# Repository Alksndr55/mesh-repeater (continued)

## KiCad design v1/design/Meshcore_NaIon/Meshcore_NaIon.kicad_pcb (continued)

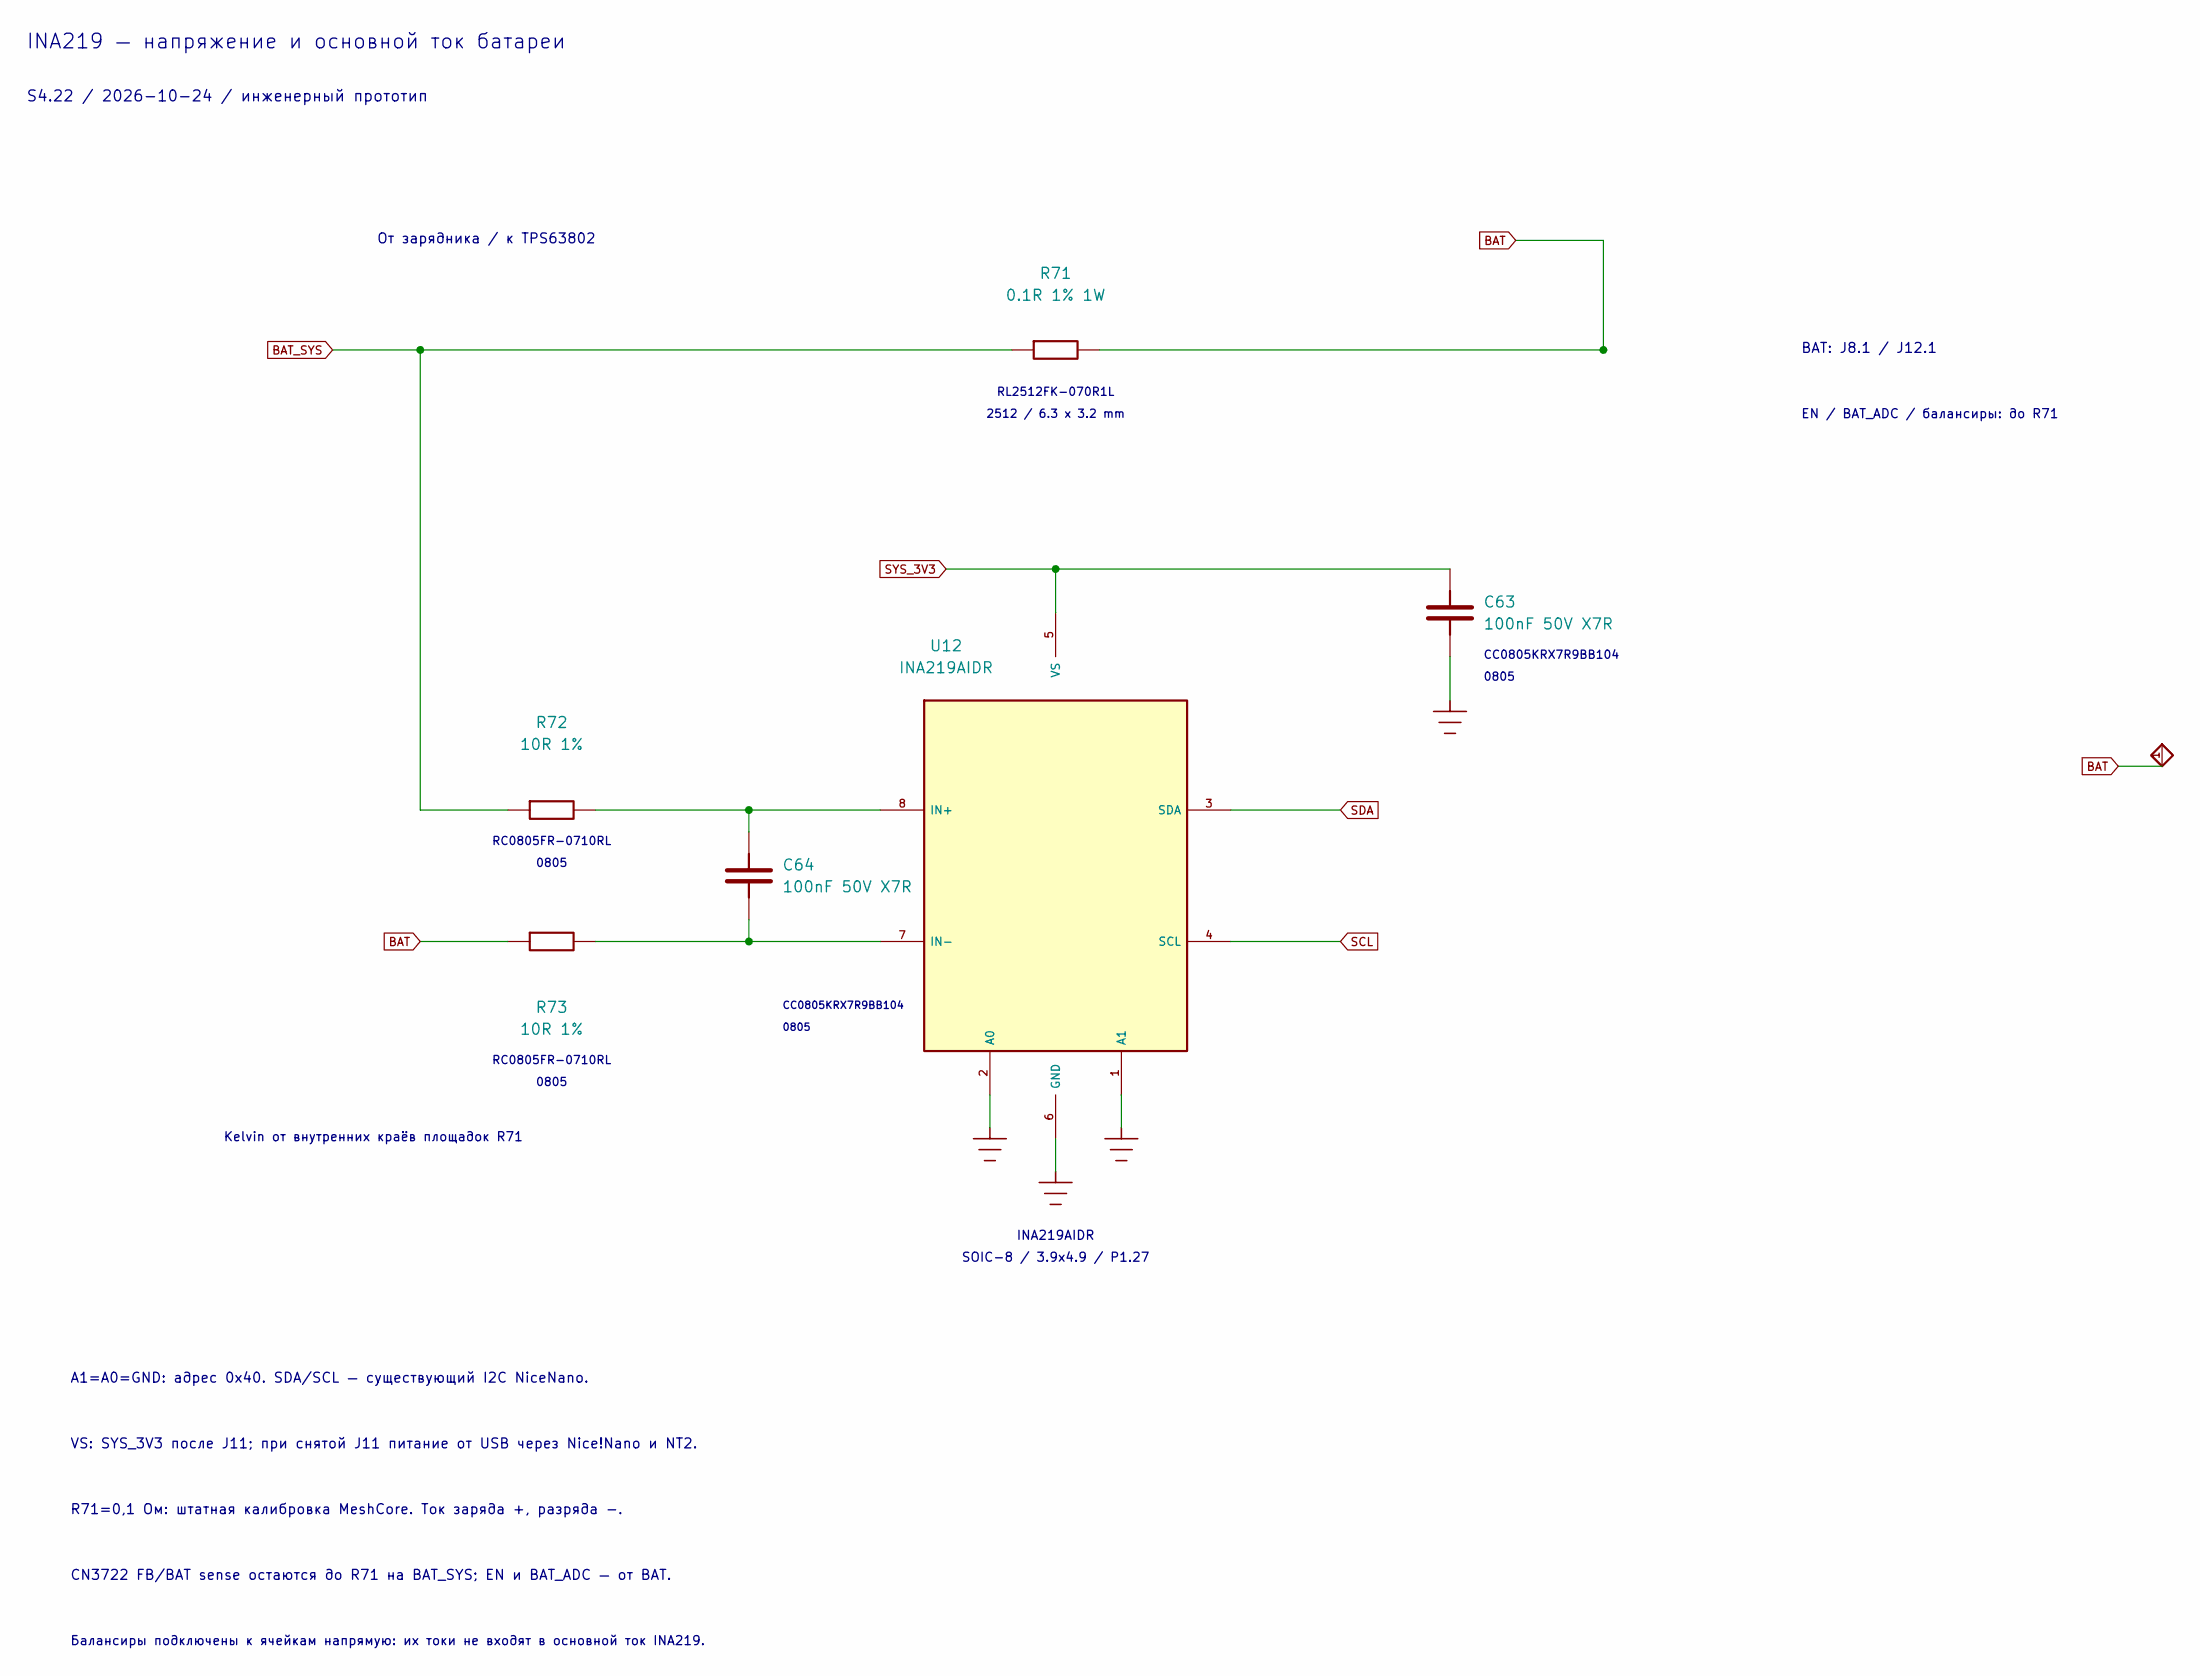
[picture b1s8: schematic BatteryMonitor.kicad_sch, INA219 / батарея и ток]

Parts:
C63, C64: 100nF 50V X7R; C_0805_2012Metric; MPN CC0805KRX7R9BB104
R71: 0.1R 1% 1W; R_2512_6332Metric__A3_R71; MPN RL2512FK-070R1L
R72, R73: 10R 1%; R_0805_2012Metric; MPN RC0805FR-0710RL
U12: INA219AIDR; SOIC-8_3.9x4.9mm_P1.27mm; MPN INA219AIDR

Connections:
BAT: R71.2, R73.1; also elsewhere on the board
BAT_SYS: R71.1, R72.1; also elsewhere on the board
GND: C63.2, U12.1 (A1), U12.2 (A0), U12.6 (GND); also elsewhere on the board
unnamed: C64.1, R72.2, U12.8 (IN+)
unnamed: C64.2, R73.2, U12.7 (IN-)
SCL: U12.4 (SCL); also elsewhere on the board
SDA: U12.3 (SDA); also elsewhere on the board
SYS_3V3: C63.1, U12.5 (VS); also elsewhere on the board

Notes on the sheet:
2512 / 6.3 x 3.2 mm
CN3722 FB/BAT sense остаются до R71 на BAT_SYS; EN и BAT_ADC — от BAT.
SOIC-8 / 3.9x4.9 / P1.27
R71=0,1 Ом: штатная калибровка MeshCore. Ток заряда +, разряда −.
CC0805KRX7R9BB104
INA219 — напряжение и основной ток батареи
Kelvin от внутренних краёв площадок R71
RL2512FK-070R1L
0805
RC0805FR-0710RL
От зарядника / к TPS63802
INA219AIDR
S4.22 / 2026-10-24 / инженерный прототип
VS: SYS_3V3 после J11; при снятой J11 питание от USB через Nice!Nano и NT2.
BAT: J8.1 / J12.1
Балансиры подключены к ячейкам напрямую: их токи не входят в основной ток INA219.
A1=A0=GND: адрес 0x40. SDA/SCL — существующий I2C NiceNano.
EN / BAT_ADC / балансиры: до R71

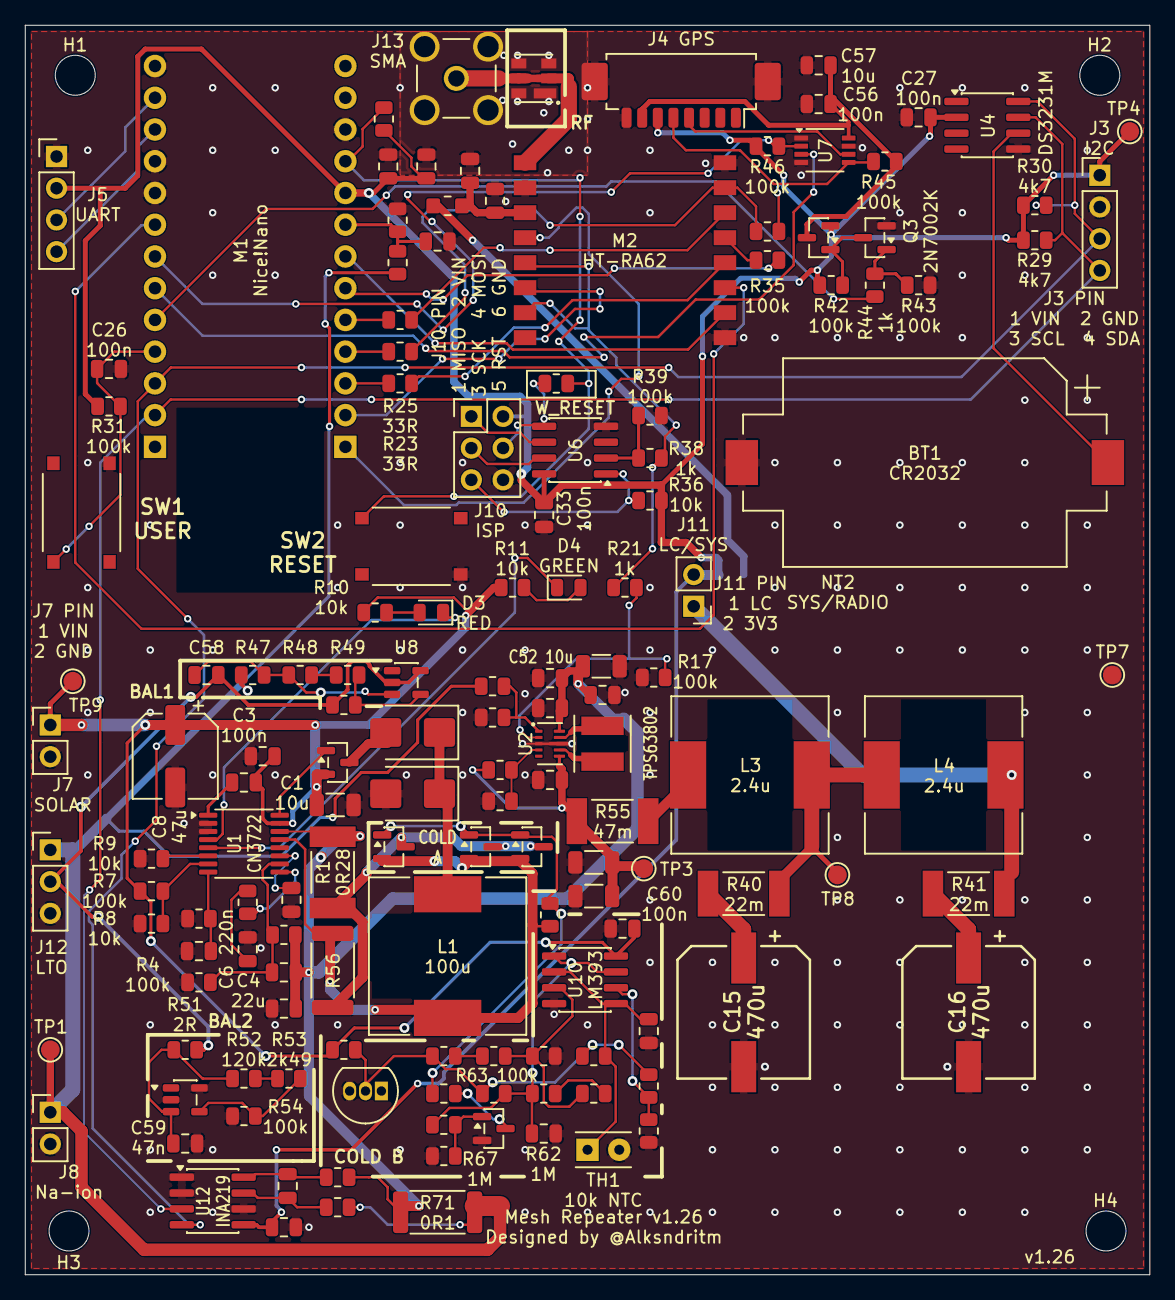
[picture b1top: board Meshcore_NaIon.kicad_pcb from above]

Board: 2 copper layers, 90.0 x 100.0 mm, 154 parts (1 on the bottom side), 90 nets.

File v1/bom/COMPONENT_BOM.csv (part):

Board,Reference,Kind,Value_NaIon_COLD,Fit_NaIon_COLD,MPN_NaIon_COLD,Value_NaIon_NoCOLD,Fit_NaIon_NoCOLD,MPN_NaIon_NoCOLD,Value_LTO_2S,Fit_LTO_2S,MPN_LTO_2S,Footprint,Layer,X_mm,Y_mm,Rotation_deg,Datasheet,Vendor_URL,Assembly,Note
MAIN,BT1,Battery,CR2032 / holder,yes,1060,CR2032 / holder,yes,1060,CR2032 / holder,yes,1060,Meshcore:BatteryHolder_Keystone_1060_1x2032,F.Cu,72.0000,35.0000,180.000,,,Na-ion: FIT; LTO 2S: FIT,Primary CR2032; no charging circuit. Holder pad1=positive; confirm assembly polarity.
MAIN,C1,C,10uF 50V X7R,yes,CL31B106KBHNNNE,10uF 50V X7R,yes,CL31B106KBHNNNE,10uF 50V X7R,yes,CL31B106KBHNNNE,Meshcore:C_1206_3216Metric,F.Cu,24.8000,62.4000,0.000,,https://www.danomsk.ru/shop/5-kondensatory/89-kondensatory-k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,Na-ion: FIT; LTO 2S: FIT,Danomsk S4.6 approved substitution. Точный текущий MPN найден в местном каталоге; входной керамический конденсатор SOLAR.
MAIN,C2,C,100nF 50V X7R,yes,CL21B104KBCNNNC,100nF 50V X7R,yes,CL21B104KBCNNNC,100nF 50V X7R,yes,CL21B104KBCNNNC,Meshcore:C_0805_2012Metric,F.Cu,19.0000,58.5000,180.000,,https://www.danomsk.ru/shop/5-kondensatory/89-kondensatory-k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,Na-ion: FIT; LTO 2S: FIT,Danomsk S4.6 approved substitution. Точный текущий MPN. C3 остаётся между SOLAR и VG; C25 остаётся в фильтре BAT_ADC.
MAIN,C3,C,100nF 50V X7R,yes,CL21B104KBCNNNC,100nF 50V X7R,yes,CL21B104KBCNNNC,100nF 50V X7R,yes,CL21B104KBCNNNC,Meshcore:C_0805_2012Metric,F.Cu,17.5000,60.6000,180.000,,https://www.danomsk.ru/shop/5-kondensatory/89-kondensatory-k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,Na-ion: FIT; LTO 2S: FIT,"VG capacitor returns to VCC, not ground Danomsk S4.6 approved substitution. Точный текущий MPN. C3 остаётся между SOLAR и VG; C25 остаётся в фильтре BAT_ADC."
MAIN,C4,C,22uF 25V X5R,yes,CL21A226MAQNNNE,22uF 25V X5R,yes,CL21A226MAQNNNE,22uF 25V X5R,yes,CL21A226MAQNNNE,Meshcore:C_0805_2012Metric,F.Cu,20.7000,78.7000,180.000,,https://www.danomsk.ru/shop/5-kondensatory/89-kondensatory-k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,Na-ion: FIT; LTO 2S: FIT,"Danomsk S4.6 approved substitution. Местный кандидат с достаточным типовым запасом: C14 при3,3V около14,90µF, инженерная оценка10,13µF против7µF минимума TPS63802. C4 при4,0V типично12,97µF, оценка8,82µF. Необходимы измерение и согласование снижения верхней температуры."
MAIN,C5,C,470pF 50V C0G,yes,CC0805JRNPO9BN471,470pF 50V C0G,yes,CC0805JRNPO9BN471,470pF 50V C0G,yes,CC0805JRNPO9BN471,Meshcore:C_0805_2012Metric,F.Cu,13.9000,74.1000,180.000,,https://www.danomsk.ru/shop/5-kondensatory/89-kondensatory-k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,Na-ion: FIT; LTO 2S: FIT,"Danomsk S4.6 approved substitution. Сохраняются ёмкость, допуск, стабильный диэлектрик и напряжение конденсатора компенсации CN3722."
MAIN,C6,C,220nF 50V X7R,yes,CC0805KKX7R9BB224,220nF 50V X7R,yes,CC0805KKX7R9BB224,220nF 50V X7R,yes,CC0805KKX7R9BB224,Meshcore:C_0805_2012Metric,F.Cu,17.8000,73.9500,90.000,,https://www.danomsk.ru/shop/5-kondensatory/89-kondensatory-k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,Na-ion: FIT; LTO 2S: FIT,"Danomsk S4.6 approved substitution. Та же ёмкость и класс X7R, тот же корпус; замена по документу производителя в карточке."
MAIN,C7,C,100nF 50V X7R,yes,CL21B104KBCNNNC,100nF 50V X7R,yes,CL21B104KBCNNNC,100nF 50V X7R,yes,CL21B104KBCNNNC,Meshcore:C_0805_2012Metric,F.Cu,21.3000,70.0000,-90.000,,https://www.danomsk.ru/shop/5-kondensatory/89-kondensatory-k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,Na-ion: FIT; LTO 2S: FIT,Danomsk S4.6 approved substitution. Точный текущий MPN. C3 остаётся между SOLAR и VG; C25 остаётся в фильтре BAT_ADC.
MAIN,C8,C,47uF 35V,yes,EEEFK1V470P,47uF 35V,yes,EEEFK1V470P,47uF 35V,yes,EEEFK1V470P,Meshcore:CP_Elec_Panasonic_FK_D_6.3x5.8,F.Cu,12.0000,58.5000,-90.000,,https://www.danomsk.ru/shop/5-kondensatory/88-kondensatory-e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,Na-ion: FIT; LTO 2S: FIT,"Panasonic FK D, 47uF35V, diameter6.3mm, height5.8mm. Exact recommended pads3.2x1.6mm, gap1.8mm. 240mArms@100kHz105C, Zmax0.36ohm@100kHz20C. Maximum105C; verify C1+C8 ripple sharing and temperature under shield. Danomsk S4.6 approved substitution. Ближайшая качественная местная замена: 240mArms@100kHz/+105°C, Zmax0,36Ω@100kHz/+20°C. Сохраняются47µF/35V/диаметр6,3мм, но это не точный температурный аналог Nichicon."
MAIN,C12,C,10uF 16V X7R,yes,CL21B106KOQNNNE,10uF 16V X7R,yes,CL21B106KOQNNNE,10uF 16V X7R,yes,CL21B106KOQNNNE,Meshcore:C_0805_2012Metric,F.Cu,42.0000,54.6500,180.000,,https://www.danomsk.ru/shop/5-kondensatory/89-kondensatory-k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,Na-ion: FIT; LTO 2S: FIT,"Danomsk S4.6 approved substitution. Предлагается местный 16V Samsung, но Cin TPS63802 должен быть не менее 4µF эффективных при максимальном BAT=4,0V. Типовая кривая даёт около6,20µF; оценка с допуском/температурой около4,74µF. Это кандидат для квалификации, не гарантированное доказательство запаса."
MAIN,C13,C,100nF 50V X7R,yes,CL21B104KBCNNNC,100nF 50V X7R,yes,CL21B104KBCNNNC,100nF 50V X7R,yes,CL21B104KBCNNNC,Meshcore:C_0805_2012Metric,F.Cu,46.2000,53.6000,0.000,,https://www.danomsk.ru/shop/5-kondensatory/89-kondensatory-k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,Na-ion: FIT; LTO 2S: FIT,"Высокочастотная развязка входа TPS63802: 100nF, 50V, X7R, 0805. Унифицированный CL21B104KBCNNNC; сохранить короткое соединение VIN-GND."
MAIN,C14,C,22uF 25V X5R,yes,CL21A226MAQNNNE,22uF 25V X5R,yes,CL21A226MAQNNNE,22uF 25V X5R,yes,CL21A226MAQNNNE,Meshcore:C_0805_2012Metric,F.Cu,42.0000,60.4000,180.000,,https://www.danomsk.ru/shop/5-kondensatory/89-kondensatory-k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,Na-ion: FIT; LTO 2S: FIT,"Local COUT before additional LC filter Danomsk S4.6 approved substitution. Местный кандидат с достаточным типовым запасом: C14 при3,3V около14,90µF, инженерная оценка10,13µF против7µF минимума TPS63802. C4 при4,0V типично12,97µF, оценка8,82µF. Необходимы измерение и согласование снижения верхней температуры."
MAIN,C15,C_POLARIZED,470uF 25V,yes,EEEFK1E471P,470uF 25V,yes,EEEFK1E471P,470uF 25V,yes,EEEFK1E471P,Meshcore:CP_Elec_10x10.2,F.Cu,57.5000,79.0000,-90.000,https://industrial.panasonic.com/cdbs/www-data/pdf/RDE0000/A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,https://www.danomsk.ru/shop/5-kondensatory/88-kondensatory-e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,Na-ion: FIT; LTO 2S: FIT,"Panasonic FK polarized SMD aluminum electrolytic, 470uF 25V +/-20%, diameter10mm, height10.2mm. One per LC stage; plus to R40/R41, minus to GND. At20C nominal minus20%=376uF. Impedance <=80mOhm and ripple850mArms at100kHz; cold/transient performance requires prototype validation."
MAIN,C16,C_POLARIZED,470uF 25V,yes,EEEFK1E471P,470uF 25V,yes,EEEFK1E471P,470uF 25V,yes,EEEFK1E471P,Meshcore:CP_Elec_10x10.2,F.Cu,75.5000,79.0000,-90.000,https://industrial.panasonic.com/cdbs/www-data/pdf/RDE0000/A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,https://www.danomsk.ru/shop/5-kondensatory/88-kondensatory-e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,Na-ion: FIT; LTO 2S: FIT,"Panasonic FK polarized SMD aluminum electrolytic, 470uF 25V +/-20%, diameter10mm, height10.2mm. One per LC stage; plus to R40/R41, minus to GND. At20C nominal minus20%=376uF. Impedance <=80mOhm and ripple850mArms at100kHz; cold/transient performance requires prototype validation."
MAIN,C21,C,10uF 16V X7R,yes,CL21B106KOQNNNE,10uF 16V X7R,yes,CL21B106KOQNNNE,10uF 16V X7R,yes,CL21B106KOQNNNE,Meshcore:C_0805_2012Metric,F.Cu,29.0500,11.3000,90.000,,https://www.danomsk.ru/shop/5-kondensatory/89-kondensatory-k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,Na-ion: FIT; LTO 2S: FIT,"Danomsk S4.6 approved substitution. Объёмная развязка питания модулей при 3,3V; повышение номинального напряжения и сохранение X7R."
MAIN,C22,C,100nF 50V X7R,yes,CL21B104KBCNNNC,100nF 50V X7R,yes,CL21B104KBCNNNC,100nF 50V X7R,yes,CL21B104KBCNNNC,Meshcore:C_0805_2012Metric,F.Cu,32.1000,11.3000,90.000,,https://www.danomsk.ru/shop/5-kondensatory/89-kondensatory-k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,Na-ion: FIT; LTO 2S: FIT,Danomsk S4.6 approved substitution. Точный текущий MPN. C3 остаётся между SOLAR и VG; C25 остаётся в фильтре BAT_ADC.
MAIN,C23,C,22uF 25V X5R,yes,CL21A226MAQNNNE,22uF 25V X5R,yes,CL21A226MAQNNNE,22uF 25V X5R,yes,CL21A226MAQNNNE,Meshcore:C_0805_2012Metric,F.Cu,35.6000,11.6500,90.000,,https://www.danomsk.ru/shop/5-kondensatory/89-kondensatory-k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,Na-ion: FIT; LTO 2S: FIT,Local22uF25V0805 radio bypass afterFB1; exactsameDanomskpartasC14. DC-biased effective capacitance requires prototype qualification.
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
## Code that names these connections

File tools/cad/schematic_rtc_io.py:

"""Compact RTC, expansion headers and shield connections."""
from schematic_core import Sheet, define, box, line, chip, PARTS

def build():
    s=Sheet('RTC_IO','DS3231M / CR2032, разъёмы и экран',4)
    define('RTC_J2_LEFT',[('1','1',-10.16,-2.54,'L','passive'),('2','2',-10.16,2.54,'L','passive')],box(-5.08,-5.08,5.08,5.08),-8.89)
    s.sym('U4',78.74,83.82)
    s.sym('BT1',30.48,91.44,label=(30.48,110.49,30.48,113.03))
    s.sym('C27',38.1,60.96,'C_V')
    for ref,x in [('R29',114.3),('R30',139.7)]:s.sym(ref,x,55.88,'R_V')
    rail_y=50.8
    s.wire((25.4,rail_y),(139.7,rail_y));s.label('SYS_3V3',(25.4,rail_y),global_=True)
    for ref in ['C27','R29','R30']:
        x,_=s.pin(ref,1);s.wire((ref,1),(x,rail_y));s.dot((x,rail_y))
    s.wire(('U4',2),(53.34,68.58),(53.34,rail_y));s.dot((53.34,rail_y))
    s.ground(('C27',2),2.54)
    s.wire(('BT1',1),(30.48,81.28),('U4',6));s.label('RTC_BAT',(38.1,81.28))
    s.ground(('BT1',2),2.54)
    for pin,ref,x,net in [(7,'R29',114.3,'SDA'),(8,'R30',139.7,'SCL')]:
        _,y=s.pin('U4',pin)
        s.wire(('U4',pin),(177.8,y));s.wire((ref,2),(x,y));s.dot((x,y))
        s.label(net,(177.8,y),180,True)
    s.nc('U4',1);s.nc('U4',3);s.nc('U4',4)
    s.wire(('U4',5),(53.34,104.14),(53.34,118.11))
    s.ground((53.34,118.11),2.54)
    s.text('CR2032: без зарядки. Установить после пайки.',15.24,132.08,1.27)
    s.text('DS3231M: SO-8; точность ±5 ppm; SQW только 1 Гц.',15.24,138.43,1.27)
    s.text('I²C: 0x68. INT/SQW не используется.',15.24,144.78,1.27)
    s.text('EOSC=0; BBSQW=0; INTCN=1; EN32kHz=0.',15.24,151.13,1.27)
    s.text('Проверять OSF; снять после установки времени.',15.24,157.48,1.27)
    for ref,x,y in [('J3',205.74,60.96),('J5',205.74,103.0)]:
        s.sym(ref,x,y)
        for pin in range(1,5):s.net(ref,pin,5.08)
    build_gps(s)
    if 'SH1' in PARTS:
        s.sym('SH1',210.82,151.13,label=(210.82,133.35,210.82,135.89))
        pts=[]
        for pin in range(1,5):
            _,y=s.pin('SH1',pin);p=(228.6,y);pts.append(p);s.wire(('SH1',pin),p)
        s.wire(*pts)
        for p in pts[1:-1]:s.dot(p)
        s.ground(pts[-1],2.54)
    for ref,x,y in [('H1',251.46,146.05),('H2',278.13,146.05),('H3',251.46,170.18),('H4',278.13,170.18)]:
        if ref in PARTS:
            s.sym(ref,x,y)
            if PARTS[ref]['nets']:s.net(ref,'1',2.54)
    s.text('Средний экран: отдельная плата 90×60; GND через стойки.',195.58,186.69,1.27)
    return s

def build_gps(s):
    # Exact P3 numbering, names always describe the GPS module direction.
    chip('GPS_J8',[(str(i),name,-12.7,(i-4.5)*5.08,'L','passive') for i,name in enumerate(['RESET_N','PPS','WAKE_UP','RXD GPS','TXD GPS','V_BCKP','VCC','GND'],1)]+[('MP','Mounts',0,30.48,'B','passive')],20.32,45.72)
    define('GPS_NMOS',[('1','G',-10.16,0,'L','input',5.08),('3','D',0,-7.62,'T','passive',2.54),('2','S',0,7.62,'B','passive',2.54)],
        line([(-5.08,0),(-2.54,0),(-2.54,-2.54),(-2.54,2.54)])+line([(-1.27,-2.54),(-1.27,2.54)])+line([(0,-5.08),(0,-1.27),(-1.27,-1.27)])+line([(0,5.08),(0,1.27),(-1.27,1.27)])+line([(0,1.27),(1.27,0),(1.27,2.54),(0,1.27)]),-12.7)
    chip('GPS_BUF',[('8','VCC GPS',-17.78,-17.78,'L','power_in'),('2','1A / MCU TX',-17.78,-7.62,'L','input'),('6','1Y / GPS RX',17.78,-7.62,'R','output'),('5','2A / GPS TX',-17.78,2.54,'L','input'),('3','2Y / MCU RX',17.78,2.54,'R','output'),('1','~{OE1}',-7.62,25.4,'B','input'),('7','~{OE2}',0,25.4,'B','input'),('4','GND',7.62,25.4,'B','power_in')],25.4,40.64)
    s.sym('J4',385,55,'GPS_J8')
    for pin in (1,2,3):s.nc('J4',pin)
    for pin in (4,5,6,7,8):s.net('J4',pin,5.08)
    s.ground(('J4','MP'),2.54)
    s.sym('Q2',270,55,'PMOS')
    s.net('Q2',2);s.net('Q2',3)
    s.sym('R42',245,77,'R_V');s.net('R42',1)
    s.sym('Q3',270,100,'GPS_NMOS',label=(280.16,98.73,280.16,101.27));s.ground(('Q3',2),2.54)
    s.wire(('Q2',1),(270,85),('Q3',3));s.wire(('R42',2),(245,85),(270,85));s.dot((270,85));s.label('GPS_GATE',(255.16,85))
    s.sym('R44',246,100,'R_H')
    s.global_stub('GPS_EN',('R44',1),(234.95,100),(234.95,132.08),(229.87,132.08))
    s.wire(('R44',2),('Q3',1))
    s.sym('R43',255.27,117,'R_V');s.wire(('R43',1),(255.27,100));s.dot((255.27,100));s.ground(('R43',2),2.54);s.label('GPS_EN_GATE',(252,100))
    s.sym('U7',330,140,'GPS_BUF')
    for pin in (8,2,6,5,3):s.net('U7',pin,5.08)
    for pin in (1,7,4):s.ground(('U7',pin),3.81)
    s.sym('R45',300,93,'R_V');s.net('R45',1);s.net('R45',2)
    s.sym('R46',300,60,'R_V');s.net('R46',1);s.net('R46',2)
    s.sym('C56',391.16,153.67,'C_V',label=(387.35,152.4,387.35,154.94));s.net('C56',1);s.ground(('C56',2),2.54)
    s.sym('C57',330,65,'C_V');s.net('C57',1);s.ground(('C57',2),2.54)
    s.flag('GPS_3V3',285.75,30.48,407)
    s.text('GPS_EN = P0.24: HIGH включено; LOW / Hi-Z выключено.',240,199,1.05)
    s.text('J4.6: резерв 3,3 В постоянно; J4.7: питание через Q2.',240,205,1.05)
    s.text('U7: Ioff; UART не подпитывает выключенный GPS.',240,211,1.05)
    s.text('J4.1 / .3: внутренние подтяжки L76K; .2 PPS не используется.',240,217,1.05)
    s.text('T114 V2.1 P3: порядок контактов; корпус кабеля проверить.',240,223,1.05)

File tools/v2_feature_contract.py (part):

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FEATURE_PATH = ROOT / "design" / "feature_ina219_vertical.json"
BASELINE_SHA256 = "478b416c5fa28fbe4cebbc594eb1b519e90cb6c393aba6f58130b6fecffdac08"
INA_SOIC_PIN_NAMES = {"1": "A1", "2": "A0", "3": "SDA", "4": "SCL", "5": "VS", "6": "GND", "7": "IN-", "8": "IN+"}
PINMAP = {"1": "FILTER_OUT", "2": "GND", "3": "FILTER_OUT", "4": "GND", "5": "FILTER_OUT", "6": "GND", "7": "SYS_3V3", "8": "GND", "9": "BAT", "10": "SDA", "11": "MODE", "12": "SCL"}
OVERRIDES = {"POWER": {"U1": {"14": "BAT_SYS"}, "R1": {"2": "BAT_SYS"}, "C4": {"1": "BAT_SYS"}, "R3": {"1": "BAT_SYS"}, "U2": {"10": "BAT_SYS"}, "C12": {"1": "BAT_SYS"}, "C13": {"1": "BAT_SYS"}, "C52": {"1": "BAT_SYS"}, "C53": {"1": "BAT_SYS"}, "C30": {"1": "BAT_SYS"}}}
NEW_NETS = {
    "U12": {"1": "GND", "2": "GND", "3": "SDA", "4": "SCL", "5": "SYS_3V3", "6": "GND", "7": "INA_VIN_M", "8": "INA_VIN_P"},
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    if set(feature.get("new_references", [])) != set(NEW_NETS) or len(feature.get("new_references", [])) != len(NEW_NETS):
        raise ValueError("Only the six declared INA219 positions may be added")
    projection = feature.get("series_projection", {})
    if {key: projection.get(key) for key in ("reference", "pins", "nets")} != {"reference": "R71", "pins": ["1", "2"], "nets": ["BAT_SYS", "BAT"]}:
        raise ValueError("Only R71 can be collapsed for the legacy projection")
    raw = feature.get("raw_battery_endpoints", [])
    if len(raw) != len(RAW_ENDPOINTS) or {tuple(x) for x in raw} != RAW_ENDPOINTS:
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    expected = dict(original_nets)
    if feature:
        for pin, net in OVERRIDES.get(board, {}).get(ref, {}).items():
            if expected.get(pin) != "BAT":
                raise ValueError("BAT_SYS override must start from an original BAT pin")
            expected[pin] = net
    return expected

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    for board, ref in (("POWER", "J101"), ("LOGIC", "J201")):
        check(board + " exact new twelve-pin interconnect nets", parts[board].get(ref, {}).get("nets") == PINMAP)
    power = parts["POWER"]
    raw = all(power.get(ref, {}).get("nets", {}).get(pin) == "BAT" for ref, pin in RAW_ENDPOINTS)
    check("Raw pack endpoints retain BAT before measurement shunt", raw)
    lower_sys = {(p["ref"], str(pin)) for p in power.values() for pin, net in p["nets"].items() if net == "SYS_3V3"}
    check("Returned SYS_3V3 powers only INA219 VS and its bypass on POWER", lower_sys == LOWER_SYS_ENDPOINTS, sorted(lower_sys))
    check("INA219 address straps fix 7-bit address 0x40", power.get("U12", {}).get("nets", {}).get("1") == "GND" and power.get("U12", {}).get("nets", {}).get("2") == "GND")
    check("J11 removable bridge remains FILTER_OUT to SYS_3V3", parts["LOGIC"].get("J11", {}).get("nets") == {"1": "FILTER_OUT", "2": "SYS_3V3"})
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
    raw, system = group("R71", "2"), group("R71", "1")
    check("Native R71 keeps raw BAT and BAT_SYS distinct without bypass", raw is not None and system is not None and raw != system)
    check("Native raw-battery endpoints stay on shunt BAT side", raw is not None and all(group(ref, pin) == raw for ref, pin in RAW_ENDPOINTS))
    check("Native Kelvin pickup follows proper shunt sides", system is not None and group("R72", "1") == system and raw is not None and group("R73", "1") == raw)
    positive, negative = group("U12", "8"), group("U12", "7")
    check("Native INA differential RC filter endpoints", positive is not None and negative is not None and len({positive, negative, raw, system}) == 4 and group("R72", "2") == positive and group("C64", "1") == positive and group("R73", "2") == negative and group("C64", "2") == negative)
    vs, filtered = group("J101", "7"), group("J101", "1")
    check("Native INA VS return is separate from lower converter FILTER_OUT", vs is not None and filtered is not None and vs != filtered and all(group(ref, pin) == vs for ref, pin in LOWER_SYS_ENDPOINTS))
    return checks


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
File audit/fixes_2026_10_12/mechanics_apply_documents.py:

"""Apply only M-01, M-02 mechanical metadata and DOC-01 to existing V2 docs."""
from pathlib import Path
import csv
import hashlib
import importlib.util
import json
import shutil
import subprocess

ROOT=Path(__file__).resolve().parents[2]
OUT=Path(__file__).parent
generator=ROOT/'tools/cad/build_v2_mechanical_library.py'
spec=importlib.util.spec_from_file_location('v2_mechanical_library',generator)
module=importlib.util.module_from_spec(spec);spec.loader.exec_module(module)
contract_path=ROOT/'docs/mechanical_selection.json'
contract=json.loads(contract_path.read_text(encoding='utf-8'))
for part in contract['parts']:
    if part.get('footprint')=='Meshcore:SW_TE_1825027_2_Side':
        part['bracket_width']=8.41
        part['model_width_before_fix_mm']=7.66
        part['model_width_after_fix_mm']=8.41
        part['model_fix']='M-02: full nominal TE bracket outer envelope; pads and courtyard unchanged.'
        part['model_fix_checked']='2026-10-12'
assert not any(a['refs'][0].startswith('J3_J5_') for a in contract['accessories'])
contract['accessories'].extend(module.copy.deepcopy(module.J3_J5_MATES))
contract['mechanical_fixes']={
    'date':'2026-10-12','findings':['M-01','M-02','DOC-01'],
    'report':'audit/fixes_2026_10_12/mechanics.json',
    'mate_envelope':'docs/mechanics/Connfly_DS1071_SCB01x4_Mated_Envelope.step',
    'mate_qualification':'Manufacturer family compatibility and dimensioned conservative envelope. The fully assembled mating depth and cable retention require hardware qualification.',
    'mate_model_local_bbox_step_mm':[1.50,-9.015,4.355,15.75,1.395,7.145],
    'mate_placements_native':{
        'J3':{'origin_mm':[86,12],'rotation_kicad_degrees':0,'pins':{'1':'SYS_3V3','2':'GND','3':'SCL','4':'SDA'}},
        'J5':{'origin_mm':[2.5,18.12],'rotation_kicad_degrees':180,'pins':{'1':'GND','2':'SYS_3V3','3':'UART_TX','4':'UART_RX'}},
    },
    'mate_removal_space_target_mm':7,
    'mate_insertion_depth_note':'Envelope assumes housing front x=1.50 mm, 0.25 mm after nominal male insulator edge. Actual seating stop and mating depth are not specified in the drawing; do not infer an exact tolerance fit from this model.',
}
contract_path.write_text(json.dumps(contract,ensure_ascii=False,indent=2)+'\n',encoding='utf-8')

path=ROOT/'bom/DAN_NEW_PARTS.csv'
with path.open(encoding='utf-8-sig',newline='') as f:
    reader=csv.DictReader(f);fields=reader.fieldnames;rows=list(reader)
assert not any(r['Refs'].startswith('J3_J5_') for r in rows)
for a in module.J3_J5_MATES:
    rows.append({'Refs':','.join(a['refs']),'MPN':a['mpn'],
       'Quantity_per_assembly':a['quantity'],'Unit':a['unit'],
       'Applicability':'Na-ion 1S and LTO 2S; cold option unchanged','Supplier':'ДАН',
       'Article':a['article'],'Purchase_URL':a['dan_url'],'Stock_observed':a['stock'],
       'Checked':a['stock_checked'],'Drawing_URL':a['source'],'Footprint':'','Notes':a['note']})
with path.open('w',encoding='utf-8-sig',newline='') as f:
    writer=csv.DictWriter(f,fieldnames=fields);writer.writeheader();writer.writerows(rows)

path=ROOT/'bom/V2_COMPONENT_BOM.csv'
with path.open(encoding='utf-8-sig',newline='') as f:
    reader=csv.DictReader(f);fields=reader.fieldnames;rows=list(reader)
model_values={p['ref']:p['value'] for board in ['Power','Logic']
    for p in json.loads((ROOT/f'design/MeshRepeater2_{board}/model.json').read_text(encoding='utf-8'))['parts']
    if p['kind']=='MountingHole'}
for row in rows:
    if row['Reference'] in model_values:
        for field in ('Value_NaIon_COLD','Value_NaIon_NoCOLD','Value_LTO_2S'):
            row[field]=model_values[row['Reference']]
    if row['Reference'] in ('J3','J5'):
        row['Note']+=' Cable mate: Connfly I-DS1071-SCB01x4; 4x Connfly T-DS1071-SC600 per connector; quantities and purchase links in bom/DAN_NEW_PARTS.csv.'
with path.open('w',encoding='utf-8-sig',newline='') as f:
    writer=csv.DictWriter(f,fieldnames=fields);writer.writeheader();writer.writerows(rows)

path=ROOT/'docs/V2_ASSEMBLY_INSTRUCTIONS_RU.md'
text=path.read_text(encoding='utf-8')
marker='## Проверка перед механической сборкой'
assert text.count(marker)==1 and '## Кабельные части J3' not in text
section='''## Кабельные части J3 / I²C и J5 / UART

Для полного комплекта внешних кабелей закупите в ДАН **два корпуса Connfly I-DS1071-SCB01x4** (артикул 208362) и **восемь гнездовых контактов T-DS1071-SC600** (артикул 201995). На каждый разъём нужен один корпус и четыре контакта. Комплект применяется ко всем трём вариантам аккумулятора. Для пяти полных сборок нужны 10 корпусов и 40 контактов без технологического запаса. Кабельные детали перечислены отдельно в `bom/DAN_NEW_PARTS.csv`.

Официальный чертёж [Connfly DS1071](https://en.connfly.com/static/upload/file/pdf/DS1071.pdf) указывает DS1021/DS1022 как ответные вилки: это одна совместимая серия со штырём 0,64 мм и шагом 2,54 мм. Корпус 1×4 имеет номинальные размеры **10,16×2,54×14,00 мм**, с общим допуском ±0,25 мм. Провода для T-DS1071-SC600: медь AWG28–22 / 0,09–0,30 мм², диаметр изоляции 1,2–1,6 мм. Матрицу обжима подбирают для этих контактов; проверяют удержание каждого контакта в корпусе.

| Контакт платы и кабельного корпуса | J3 / I²C | J5 / UART |
|---|---|---|
| 1 | SYS_3V3 | GND |
| 2 | GND | SYS_3V3 |
| 3 | SCL | UART_TX, выход MCU |
| 4 | SDA | UART_RX, вход MCU |

Розетки без ключа: пометьте первый контакт обоих корпусов и проверьте нумерацию мультиметром относительно контактов платы до первого включения. J3 и J5 имеют различный порядок питания; одинаковый корпус не делает кабели взаимозаменяемыми. UART_TX платы подключают к RX внешнего устройства, UART_RX платы — к его TX.

Разъёмы входят горизонтально с внешних боковых краёв собранного LOGIC. Размерная модель `docs/mechanics/Connfly_DS1071_SCB01x4_Mated_Envelope.step` учитывает максимальный наружный габарит корпуса **10,41×2,79×14,25 мм** по допускам. Для прямого снятия предусмотрите по внешней стороне минимум **7 мм** свободного хода сверх установленного корпуса. Модель является оценкой наружного контура: точный упор, глубина посадки, инструмент обжима и удержание реального кабеля проверяются на образце.

'''
path.write_text(text.replace(marker,section+marker),encoding='utf-8')
print('Updated mechanical selection, cable accessory BOM, mounting values and assembly instructions.')
